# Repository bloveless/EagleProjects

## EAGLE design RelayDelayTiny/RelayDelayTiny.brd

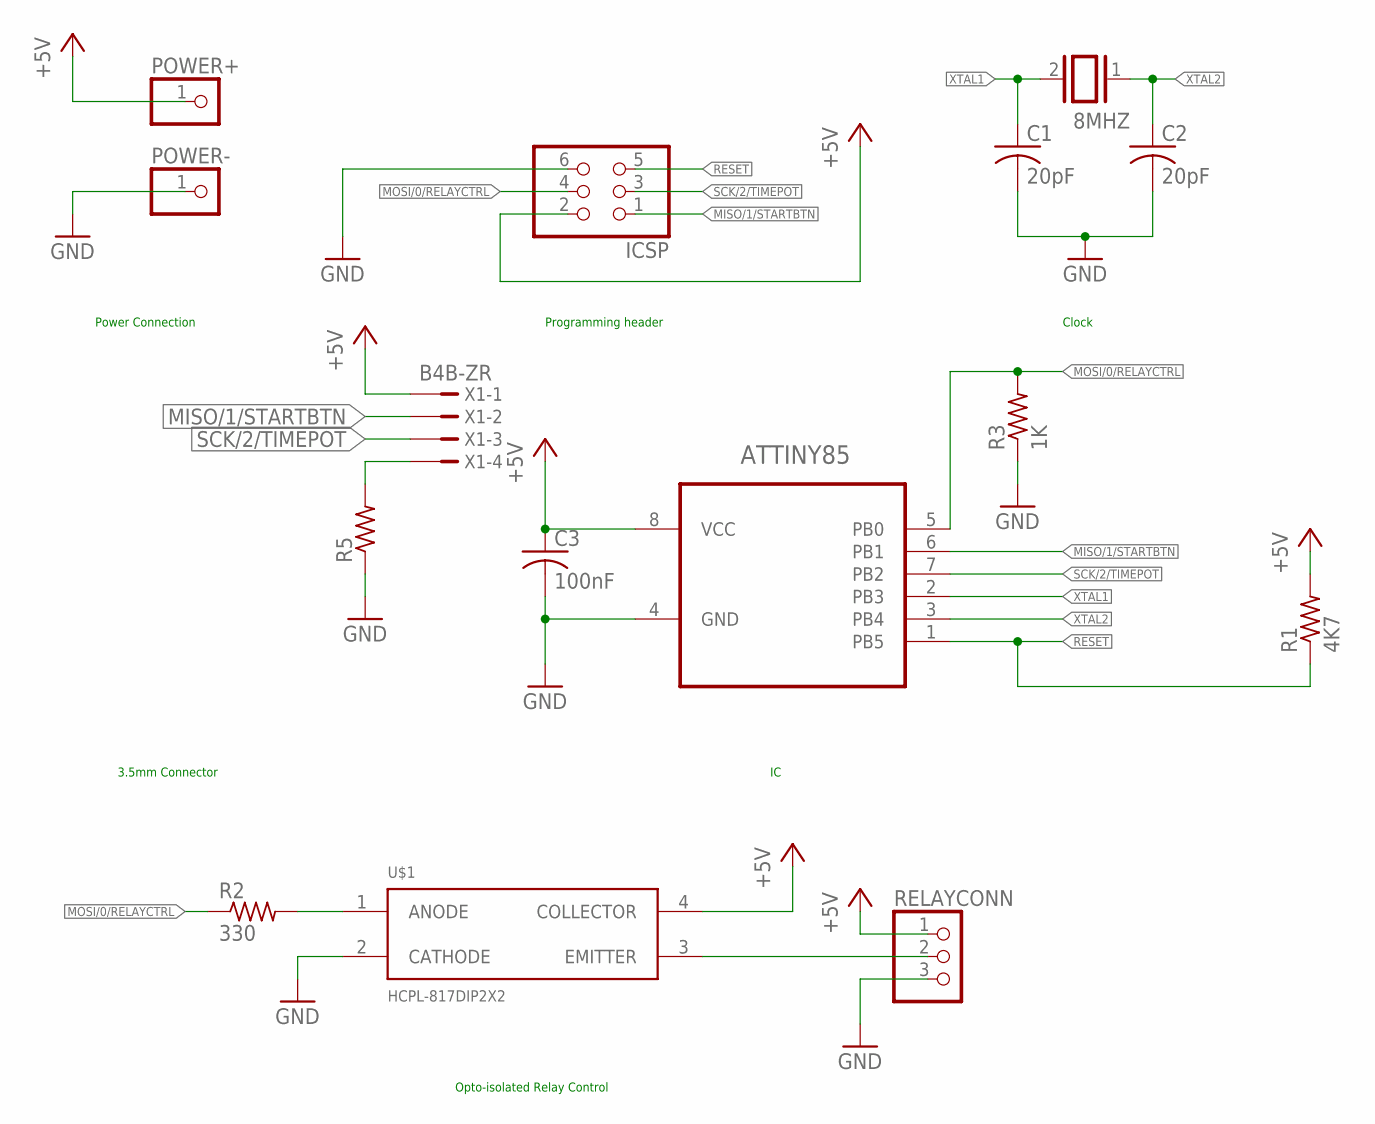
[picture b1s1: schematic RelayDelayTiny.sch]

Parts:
8MHZ: XTAL/S; QS
ATTINY85: ATTINY85-20SU; SOIC127P798X216-8N
C1, C2: 20pF; C0805
C3: 100nF; C0805
ICSP: PINHD-2X3; 2X03
POWER+: PINHD-1X1; 1X01
POWER-: PINHD-1X1; 1X01
R1: 4K7; R0805
R2: 330; M0805
R3: 1K; M0805
R5: R-US_R0805; R0805
RELAYCONN: PINHD-1X3; 1X03
U$1: HCPL-817DIP2X2; DIP
X1: B4B-ZR

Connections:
+5V: ATTINY85.8 (VCC), C3.1, ICSP.2, POWER+.1, R1.2, RELAYCONN.1, U$1.4 (COLLECTOR), X1.1
GND: ATTINY85.4 (GND), C1.2, C2.2, C3.2, ICSP.6, POWER-.1, R3.1, R5.1, RELAYCONN.3, U$1.2 (CATHODE)
MISO/1/STARTBTN: ATTINY85.6 (PB1), ICSP.1, X1.2
MOSI/0/RELAYCTRL: ATTINY85.5 (PB0), ICSP.4, R2.1, R3.2
unnamed: RELAYCONN.2, U$1.3 (EMITTER)
unnamed: R2.2, U$1.1 (ANODE)
unnamed: R5.2, X1.4
RESET: ATTINY85.1 (PB5), ICSP.5, R1.1
SCK/2/TIMEPOT: ATTINY85.7 (PB2), ICSP.3, X1.3
XTAL1: 8MHZ.2, ATTINY85.2 (PB3), C1.1
XTAL2: 8MHZ.1, ATTINY85.3 (PB4), C2.1

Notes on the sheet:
Programming header
Clock
3.5mm Connector
Opto-isolated Relay Control
Power Connection

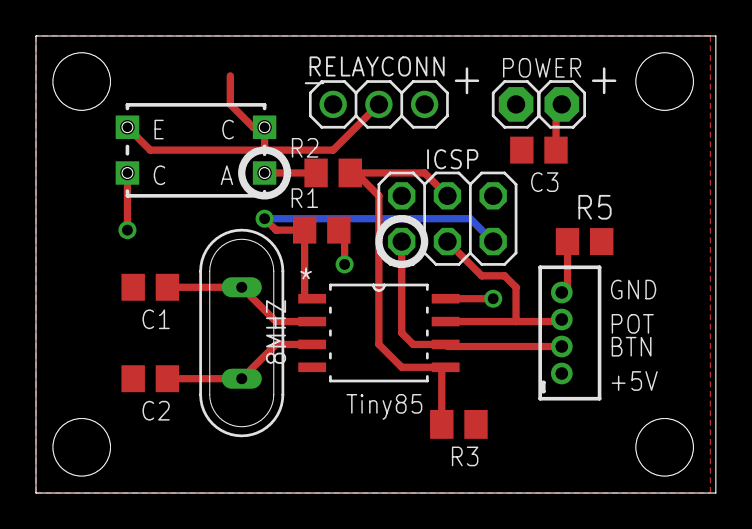
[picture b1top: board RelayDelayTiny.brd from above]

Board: 2 copper layers, 37.8 x 25.4 mm, 15 parts (0 on the bottom side), 11 nets.

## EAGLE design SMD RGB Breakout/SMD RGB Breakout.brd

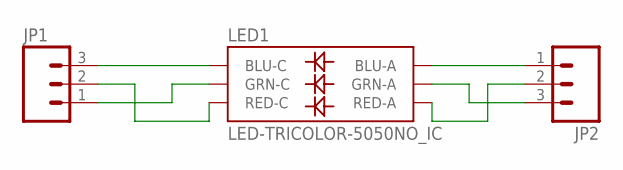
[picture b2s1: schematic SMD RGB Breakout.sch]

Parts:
JP1, JP2: M03PTH; 1X03
LED1: LED-TRICOLOR-5050NO_IC; LED-TRICOLOR-5050

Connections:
unnamed: JP1.3, LED1.4 (BLU-C)
unnamed: JP1.1, LED1.6 (GRN-C)
unnamed: JP1.2, LED1.5 (RED-C)
unnamed: JP2.1, LED1.3 (BLU-A)
unnamed: JP2.3, LED1.1 (GRN-A)
unnamed: JP2.2, LED1.2 (RED-A)

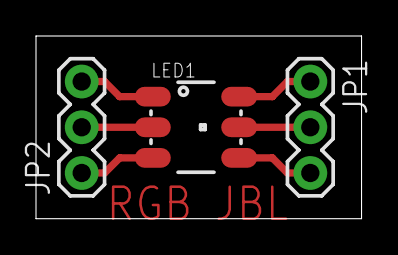
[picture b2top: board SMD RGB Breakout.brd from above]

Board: 2 copper layers, 18.1 x 10.2 mm, 3 parts (0 on the bottom side), 6 nets.

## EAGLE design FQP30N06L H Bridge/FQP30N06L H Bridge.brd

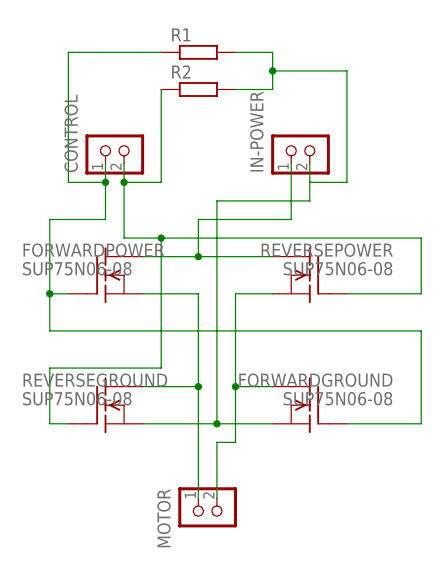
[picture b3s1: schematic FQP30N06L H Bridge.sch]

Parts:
CONTROL: CON_HEADER_1X02-PTH; M1X2
FORWARDGROUND: SUP75N06-08; TO220
FORWARDPOWER: SUP75N06-08; TO220
IN-POWER: CON_HEADER_1X02-PTH; M1X2
MOTOR: CON_HEADER_1X02-PTH; M1X2
R1, R2: RESISTOR-PTH-0.4; RTH025W
REVERSEGROUND: SUP75N06-08; TO220
REVERSEPOWER: SUP75N06-08; TO220

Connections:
unnamed: CONTROL.2, R2.1, REVERSEGROUND.1 (G), REVERSEPOWER.1 (G)
unnamed: CONTROL.1, FORWARDGROUND.1 (G), FORWARDPOWER.1 (G), R1.1
unnamed: FORWARDGROUND.3 (S), IN-POWER.2, R1.2, R2.2, REVERSEGROUND.3 (S)
unnamed: FORWARDPOWER.2 (D), IN-POWER.1, REVERSEPOWER.2 (D)
unnamed: FORWARDPOWER.3 (S), MOTOR.1, REVERSEGROUND.2 (D)
unnamed: FORWARDGROUND.2 (D), MOTOR.2, REVERSEPOWER.3 (S)

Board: 2 copper layers, 9 parts (0 on the bottom side), 6 nets, no tracks yet.

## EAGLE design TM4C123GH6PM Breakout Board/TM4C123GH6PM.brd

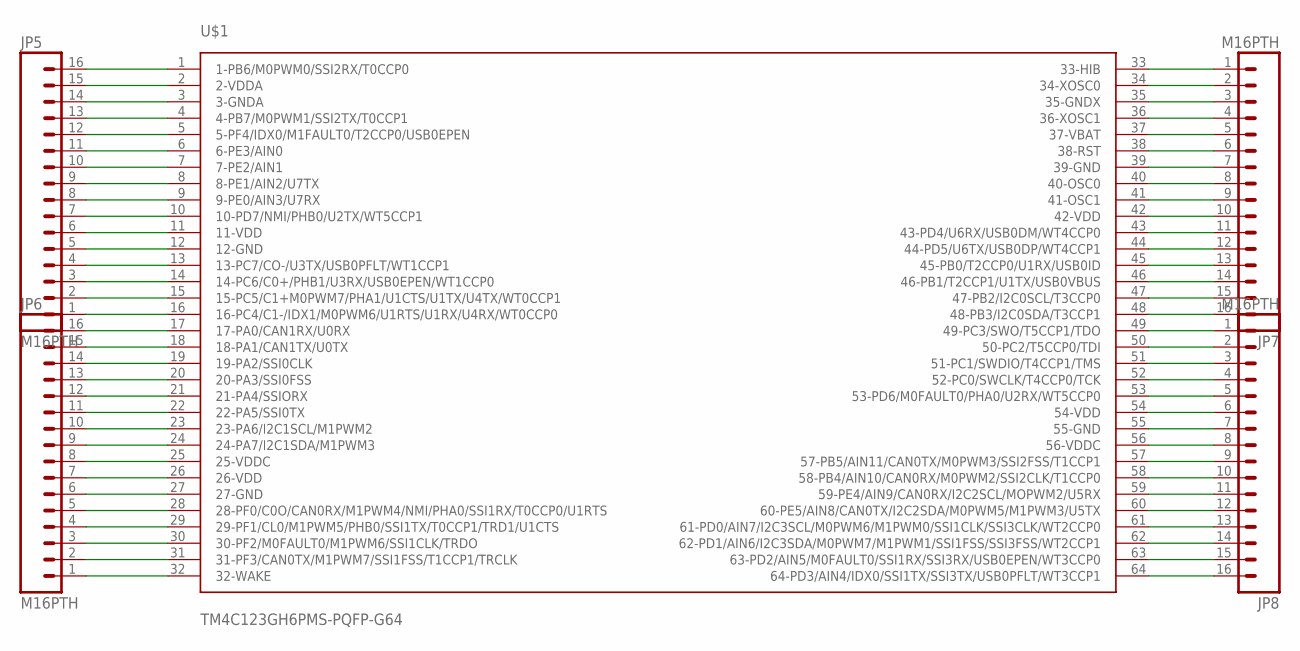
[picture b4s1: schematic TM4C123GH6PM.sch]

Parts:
JP5, JP6, JP7, JP8: M16PTH; 1X16
U$1: TM4C123GH6PMS-PQFP-G64; LQFP

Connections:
unnamed: JP5.16, U$1.1 (1-PB6/M0PWM0/SSI2RX/T0CCP0)
unnamed: JP5.15, U$1.2 (2-VDDA)
unnamed: JP5.14, U$1.3 (3-GNDA)
unnamed: JP5.13, U$1.4 (4-PB7/M0PWM1/SSI2TX/T0CCP1)
unnamed: JP5.12, U$1.5 (5-PF4/IDX0/M1FAULT0/T2CCP0/USB0EPEN)
unnamed: JP5.11, U$1.6 (6-PE3/AIN0)
unnamed: JP5.10, U$1.7 (7-PE2/AIN1)
unnamed: JP5.9, U$1.8 (8-PE1/AIN2/U7TX)
unnamed: JP5.8, U$1.9 (9-PE0/AIN3/U7RX)
unnamed: JP5.7, U$1.10 (10-PD7/NMI/PHB0/U2TX/WT5CCP1)
unnamed: JP5.6, U$1.11 (11-VDD)
unnamed: JP5.5, U$1.12 (12-GND)
unnamed: JP5.4, U$1.13 (13-PC7/CO-/U3TX/USB0PFLT/WT1CCP1)
unnamed: JP5.3, U$1.14 (14-PC6/C0+/PHB1/U3RX/USB0EPEN/WT1CCP0)
unnamed: JP5.2, U$1.15 (15-PC5/C1+M0PWM7/PHA1/U1CTS/U1TX/U4TX/W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)
unnamed: JP5.1, U$1.16 (16-PC4/C1-/IDX1/M0PWM6/U1RTS/U1RX/U4RX/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)
unnamed: JP6.16, U$1.17 (17-PA0/CAN1RX/U0RX)
unnamed: JP6.15, U$1.18 (18-PA1/CAN1TX/U0TX)
unnamed: JP6.14, U$1.19 (19-PA2/SSI0CLK)
unnamed: JP6.13, U$1.20 (20-PA3/SSI0FSS)
unnamed: JP6.12, U$1.21 (21-PA4/SSIORX)
unnamed: JP6.11, U$1.22 (22-PA5/SSI0TX)
unnamed: JP6.10, U$1.23 (23-PA6/I2C1SCL/M1PWM2)
unnamed: JP6.9, U$1.24 (24-PA7/I2C1SDA/M1PWM3)
unnamed: JP6.8, U$1.25 (25-VDDC)
unnamed: JP6.7, U$1.26 (26-VDD)
unnamed: JP6.6, U$1.27 (27-GND)
unnamed: JP6.5, U$1.28 (28-PF0/C0O/CAN0RX/M1PWM4/NMI/PHA0/SSI1R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)
unnamed: JP6.4, U$1.29 (29-PF1/CL0/M1PWM5/PHB0/SSI1TX/T0CCP1/TR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)
unnamed: JP6.3, U$1.30 (30-PF2/M0FAULT0/M1PWM6/SSI1CLK/TRDO)
unnamed: JP6.2, U$1.31 (31-PF3/CAN0TX/M1PWM7/SSI1FSS/T1CCP1/TRC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)
unnamed: JP6.1, U$1.32 (32-WAKE)
unnamed: JP7.1, U$1.33 (33-HIB)
unnamed: JP7.2, U$1.34 (34-XOSC0)
unnamed: JP7.3, U$1.35 (35-GNDX)
unnamed: JP7.4, U$1.36 (36-XOSC1)
unnamed: JP7.5, U$1.37 (37-VBAT)
unnamed: JP7.6, U$1.38 (38-RST)
unnamed: JP7.7, U$1.39 (39-GND)
unnamed: JP7.8, U$1.40 (40-OSC0)
unnamed: JP7.9, U$1.41 (41-OSC1)
unnamed: JP7.10, U$1.42 (42-VDD)
unnamed: JP7.11, U$1.43 (43-PD4/U6RX/USB0DM/WT4CCP0)
unnamed: JP7.12, U$1.44 (44-PD5/U6TX/USB0DP/WT4CCP1)
unnamed: JP7.13, U$1.45 (45-PB0/T2CCP0/U1RX/USB0ID)
unnamed: JP7.14, U$1.46 (46-PB1/T2CCP1/U1TX/USB0VBUS)
unnamed: JP7.15, U$1.47 (47-PB2/I2C0SCL/T3CCP0)
unnamed: JP7.16, U$1.48 (48-PB3/I2C0SDA/T3CCP1)
unnamed: JP8.1, U$1.49 (49-PC3/SWO/T5CCP1/TDO)
unnamed: JP8.2, U$1.50 (50-PC2/T5CCP0/TDI)
unnamed: JP8.3, U$1.51 (51-PC1/SWDIO/T4CCP1/TMS)
unnamed: JP8.4, U$1.52 (52-PC0/SWCLK/T4CCP0/TCK)
unnamed: JP8.5, U$1.53 (53-PD6/M0FAULT0/PHA0/U2RX/WT5CCP0)
unnamed: JP8.6, U$1.54 (54-VDD)
unnamed: JP8.7, U$1.55 (55-GND)
unnamed: JP8.8, U$1.56 (56-VDDC)
unnamed: JP8.9, U$1.57 (57-PB5/AIN11/CAN0TX/M0PWM3/SSI2FSS/T1CC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)
unnamed: JP8.10, U$1.58 (58-PB4/AIN10/CAN0RX/M0PWM2/SSI2CLK/T1CC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)
unnamed: JP8.11, U$1.59 (59-PE4/AIN9/CAN0RX/I2C2SCL/MOPWM2/U5RX)
unnamed: JP8.12, U$1.60 (60-PE5/AIN8/CAN0TX/I2C2SDA/M0PWM5/M1PWM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)
unnamed: JP8.13, U$1.61 (61-PD0/AIN7/I2C3SCL/M0PWM6/M1PWM0/SSI1C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)
unnamed: JP8.14, U$1.62 (62-PD1/AIN6/I2C3SDA/M0PWM7/M1PWM1/SSI1F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)
unnamed: JP8.15, U$1.63 (63-PD2/AIN5/M0FAULT0/SSI1RX/SSI3RX/USB0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)
unnamed: JP8.16, U$1.64 (64-PD3/AIN4/IDX0/SSI1TX/SSI3TX/USB0PFLT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)

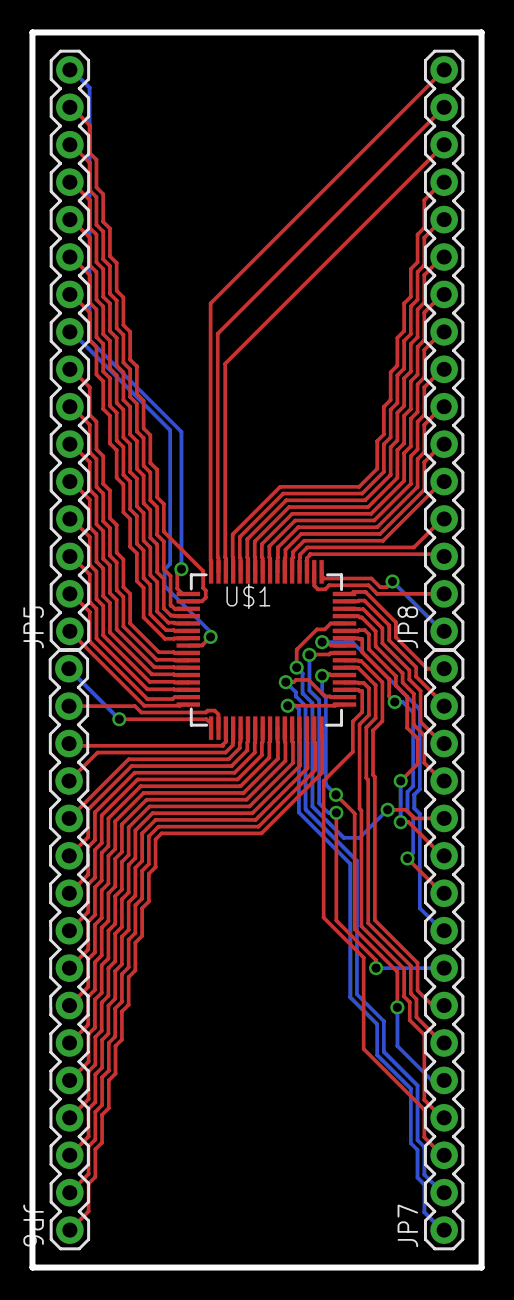
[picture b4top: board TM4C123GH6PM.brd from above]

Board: 2 copper layers, 30.5 x 83.8 mm, 5 parts (0 on the bottom side), 64 nets.

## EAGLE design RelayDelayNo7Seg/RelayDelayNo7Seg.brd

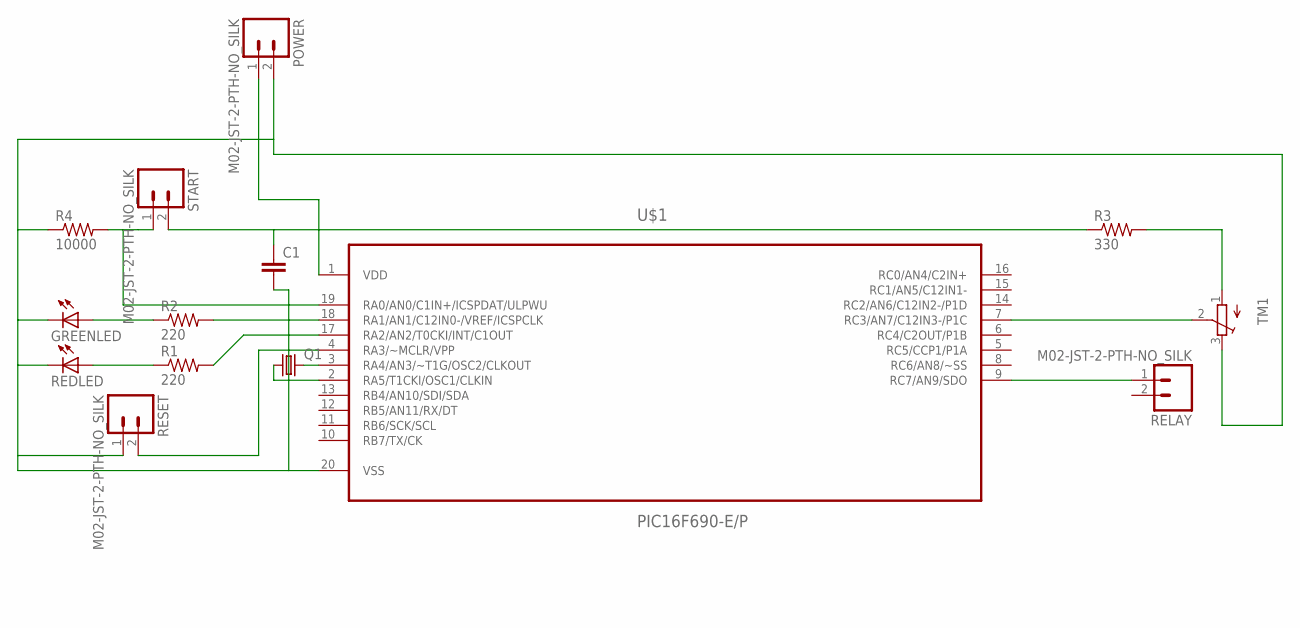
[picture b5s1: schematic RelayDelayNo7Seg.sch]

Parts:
C1: CAPEZ; CAP-PTH-SMALLEZ
GREENLED: LED5MM
POWER: M02-JST-2-PTH-NO_SILK; JST-2-PTH-NS
Q1: CRYSTALHC49S; HC49/S
R1, R2: 220; 0204V
R3: 330; 0204V
R4: 10000; 0204V
REDLED: LED5MM
RELAY: M02-JST-2-PTH-NO_SILK; JST-2-PTH-NS
RESET: M02-JST-2-PTH-NO_SILK; JST-2-PTH-NS
START: M02-JST-2-PTH-NO_SILK; JST-2-PTH-NS
TM1: TRIMPOT3386; TRIM-3386
U$1: PIC16F690-E/P; DIP254P762X533-20

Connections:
unnamed: R2.2, U$1.18 (RA1/AN1/C12IN0-/VREF/ICSPCLK)
unnamed: GREENLED.A, R2.1
unnamed: R1.2, U$1.17 (RA2/AN2/T0CKI/INT/C1OUT)
unnamed: R1.1, REDLED.A
unnamed: TM1.2 (S), U$1.7 (RC3/AN7/C12IN3-/P1C)
unnamed: R3.2, TM1.1 (A)
unnamed: RESET.2, U$1.4 (RA3/~MCLR/VPP)
unnamed: Q1.1, U$1.2 (RA5/T1CKI/OSC1/CLKIN)
unnamed: R4.2, START.1, U$1.19 (RA0/AN0/C1IN+/ICSPDAT/ULPWU)
unnamed: RELAY.1, U$1.9 (RC7/AN9/SDO)
unnamed: Q1.2, U$1.3 (RA4/AN3/~T1G/OSC2/CLKOUT)
unnamed: C1.1, POWER.1, R3.1, START.2, U$1.1 (VDD)
unnamed: C1.2, GREENLED.K (C), POWER.2, R4.1, REDLED.K (C), RESET.1, TM1.3 (E), U$1.20 (VSS)

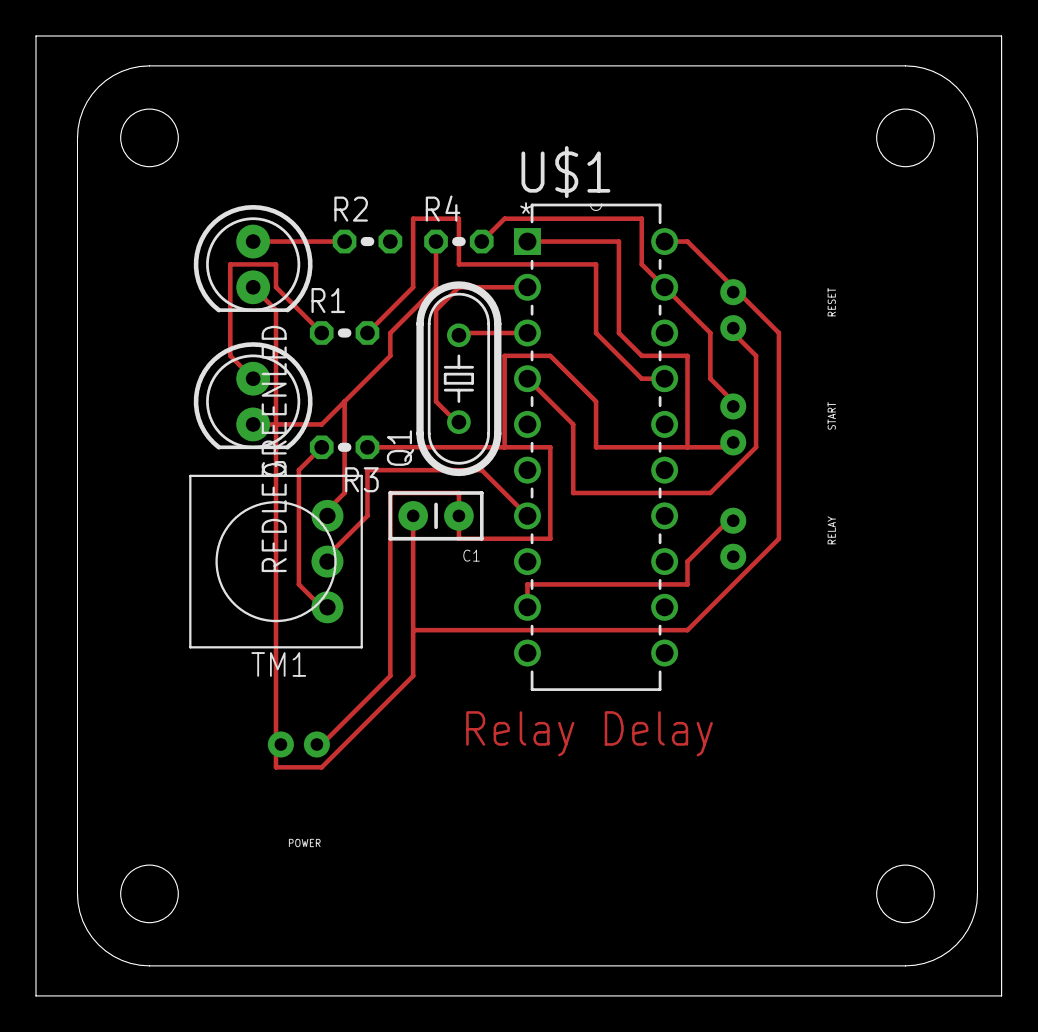
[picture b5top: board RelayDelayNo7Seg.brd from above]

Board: 2 copper layers, 53.6 x 53.3 mm, 15 parts (0 on the bottom side), 13 nets.

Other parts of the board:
U$2: DP5050_V1

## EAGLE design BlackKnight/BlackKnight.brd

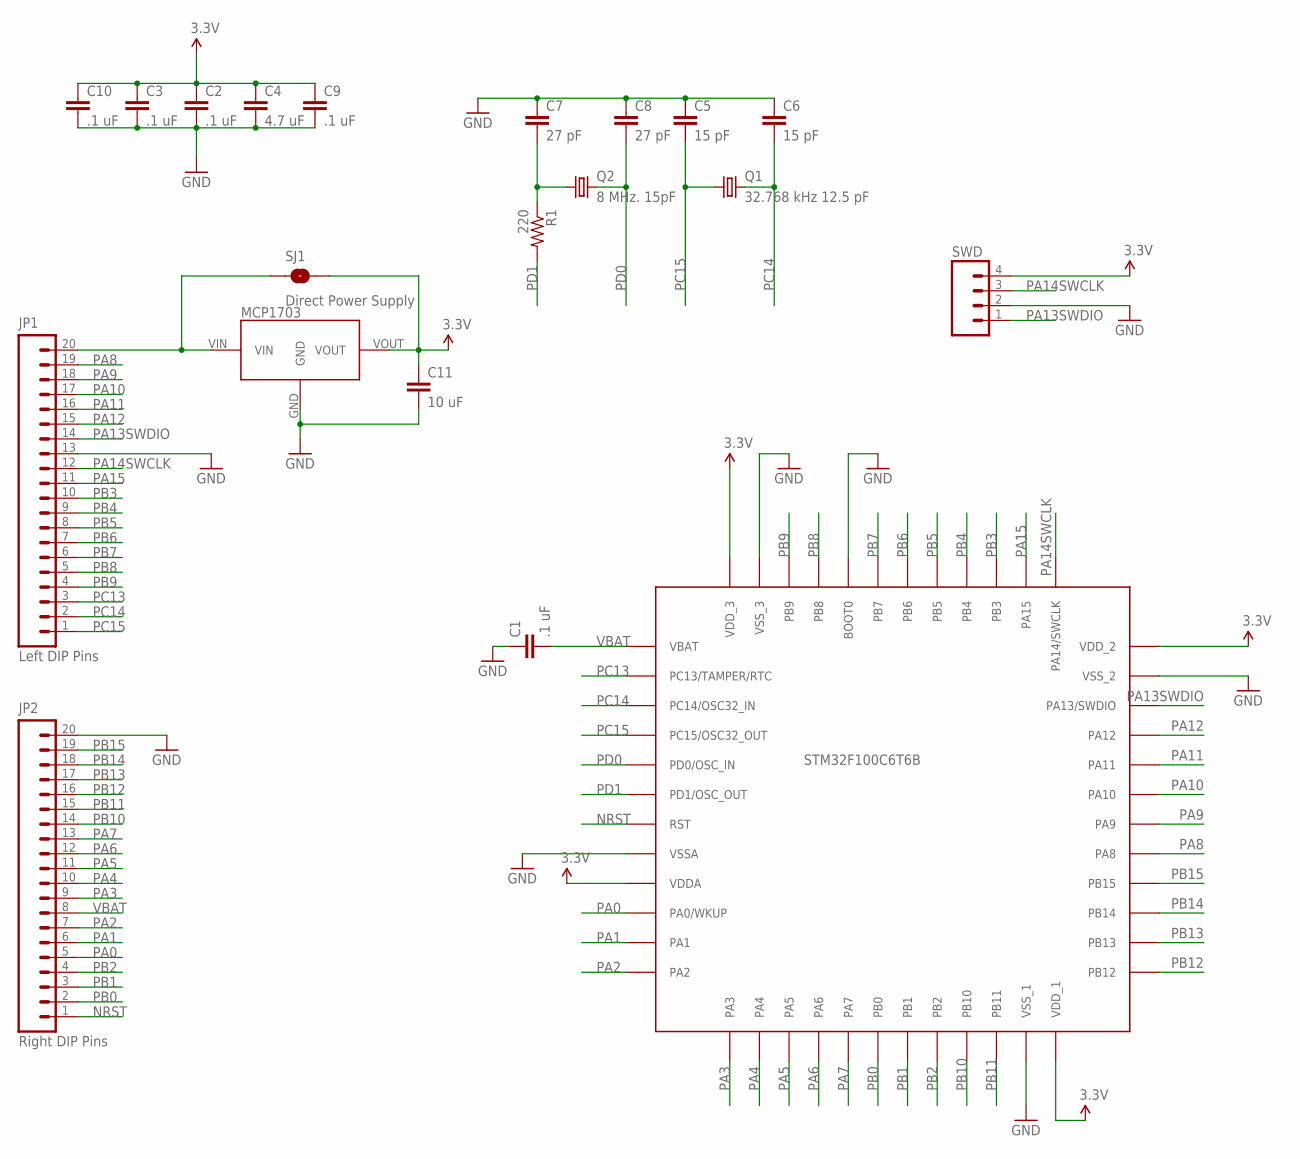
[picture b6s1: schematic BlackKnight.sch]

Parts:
C1, C2, C3, C9, C10: .1 uF; 0805
C4: 4.7 uF; 0805
C5, C6: 15 pF; 0805
C7, C8: 27 pF; 0805
C11: 10 uF; 0805
JP1: Left DIP Pins; 1X20
JP2: Right DIP Pins; 1X20
MCP1703: MCP1703; SOT-89
Q1: 32.768 kHz 12.5 pF; TC26H
Q2: 8 MHz. 15pF; HC49U-V
R1: 220; 0805
SJ1: Direct Power Supply; SJ_2S-NO
STM32F100C6T6B: STM32F100C6T6B; 48-LQFP
SWD: M04LOCK; 1X04_LOCK

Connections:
3.3V: C2.1, C3.1, C4.1, C9.1, C10.1, C11.1, MCP1703.VOUT, SJ1.2, STM32F100C6T6B.VDDA, STM32F100C6T6B.VDD_1, STM32F100C6T6B.VDD_2, STM32F100C6T6B.VDD_3, SWD.4
GND: C1.1, C2.2, C3.2, C4.2, C5.1, C6.1, C7.1, C8.1, C9.2, C10.2, C11.2, JP1.13, JP2.20, MCP1703.GND, STM32F100C6T6B.BOOT0, STM32F100C6T6B.VSSA, STM32F100C6T6B.VSS_1, STM32F100C6T6B.VSS_2, STM32F100C6T6B.VSS_3, SWD.2
unnamed: JP1.20, MCP1703.VIN, SJ1.1
unnamed: C7.2, Q2.1, R1.1
NRST: JP2.1, STM32F100C6T6B.RST
PA0: JP2.5, STM32F100C6T6B.PA0/WKUP
PA1: JP2.6, STM32F100C6T6B.PA1
PA2: JP2.7, STM32F100C6T6B.PA2
PA3: JP2.9, STM32F100C6T6B.PA3
PA4: JP2.10, STM32F100C6T6B.PA4
PA5: JP2.11, STM32F100C6T6B.PA5
PA6: JP2.12, STM32F100C6T6B.PA6
PA7: JP2.13, STM32F100C6T6B.PA7
PA8: JP1.19, STM32F100C6T6B.PA8
PA9: JP1.18, STM32F100C6T6B.PA9
PA10: JP1.17, STM32F100C6T6B.PA10
PA11: JP1.16, STM32F100C6T6B.PA11
PA12: JP1.15, STM32F100C6T6B.PA12
PA13SWDIO: JP1.14, STM32F100C6T6B.PA13/SWDIO, SWD.1
PA14SWCLK: JP1.12, STM32F100C6T6B.PA14/SWCLK, SWD.3
PA15: JP1.11, STM32F100C6T6B.PA15
PB0: JP2.2, STM32F100C6T6B.PB0
PB1: JP2.3, STM32F100C6T6B.PB1
PB2: JP2.4, STM32F100C6T6B.PB2
PB3: JP1.10, STM32F100C6T6B.PB3
PB4: JP1.9, STM32F100C6T6B.PB4
PB5: JP1.8, STM32F100C6T6B.PB5
PB6: JP1.7, STM32F100C6T6B.PB6
PB7: JP1.6, STM32F100C6T6B.PB7
PB8: JP1.5, STM32F100C6T6B.PB8
PB9: JP1.4, STM32F100C6T6B.PB9
PB10: JP2.14, STM32F100C6T6B.PB10
PB11: JP2.15, STM32F100C6T6B.PB11
PB12: JP2.16, STM32F100C6T6B.PB12
PB13: JP2.17, STM32F100C6T6B.PB13
PB14: JP2.18, STM32F100C6T6B.PB14
PB15: JP2.19, STM32F100C6T6B.PB15
PC13: JP1.3, STM32F100C6T6B.PC13/TAMPER/RTC
PC14: C6.2, JP1.2, Q1.2, STM32F100C6T6B.PC14/OSC32_IN
PC15: C5.2, JP1.1, Q1.1, STM32F100C6T6B.PC15/OSC32_OUT
PD0: C8.2, Q2.2, STM32F100C6T6B.PD0/OSC_IN
PD1: R1.2, STM32F100C6T6B.PD1/OSC_OUT
VBAT: C1.2, JP2.8, STM32F100C6T6B.VBAT

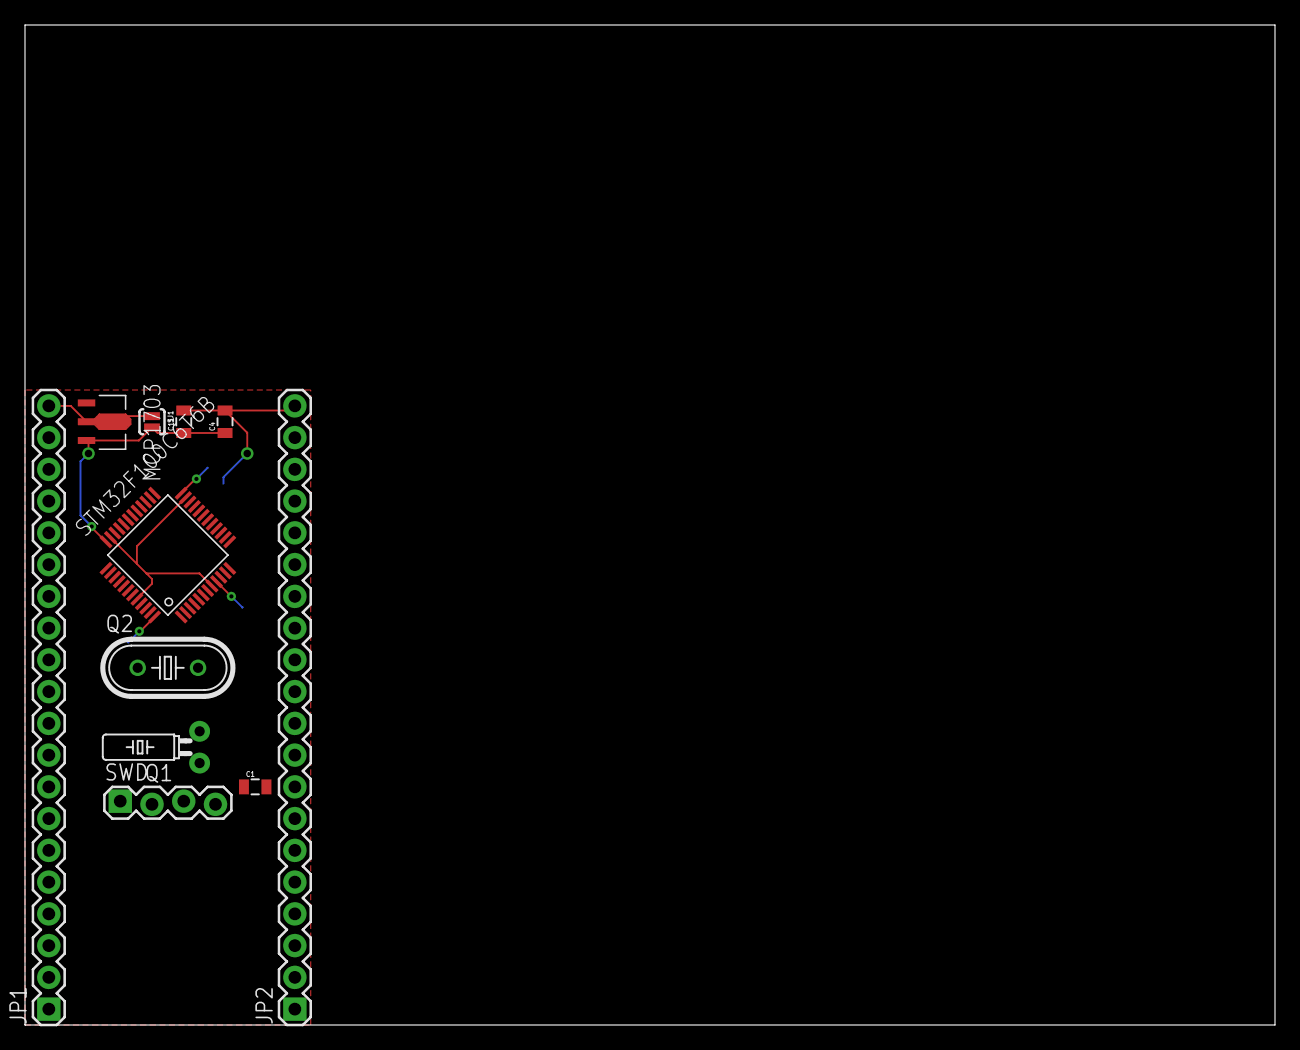
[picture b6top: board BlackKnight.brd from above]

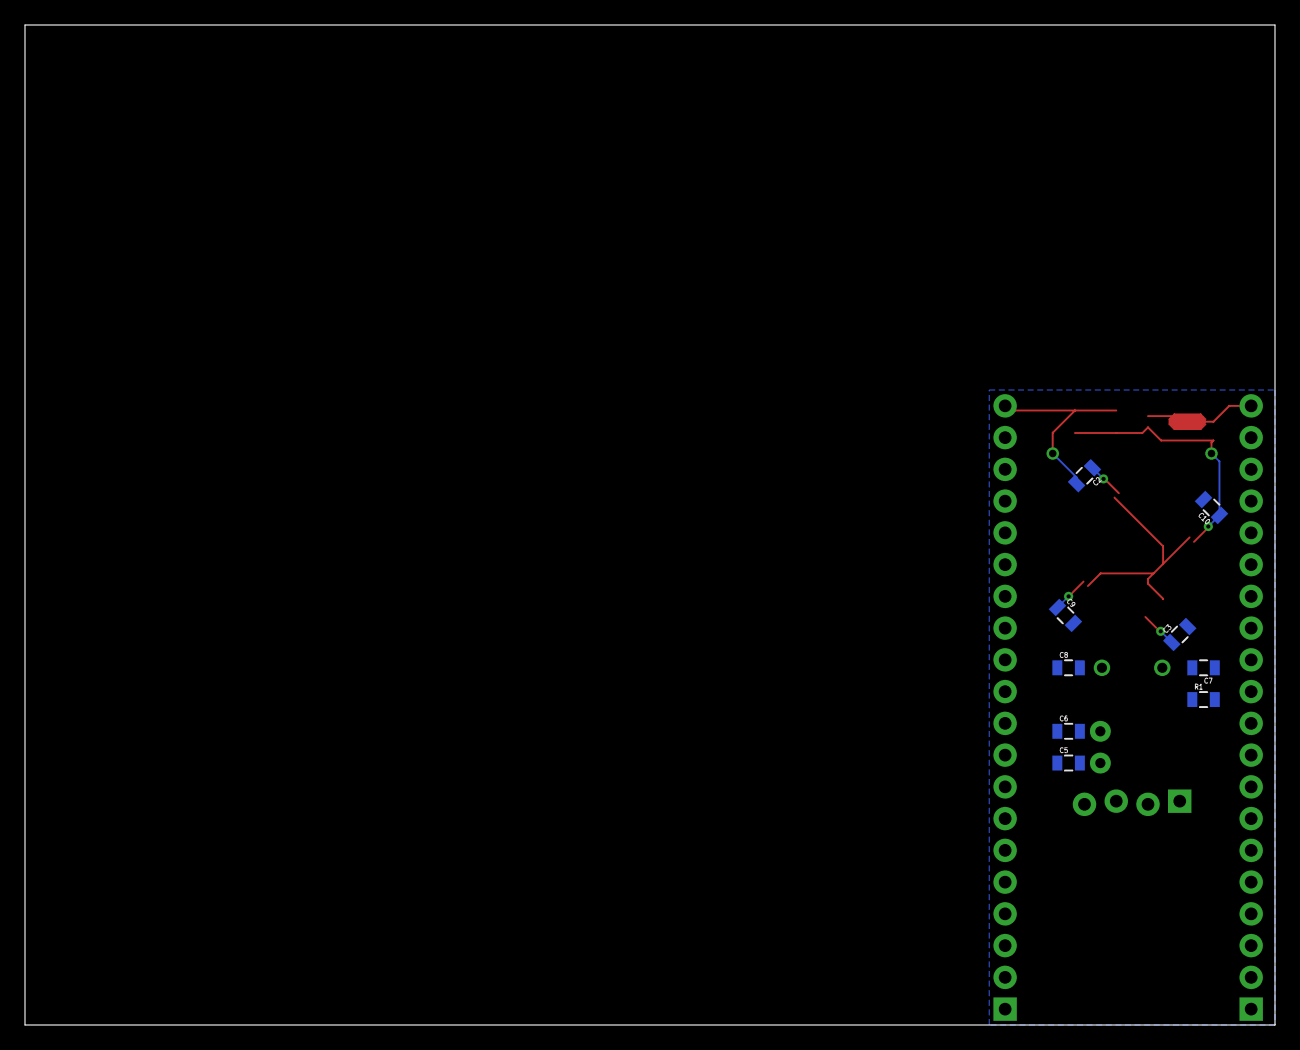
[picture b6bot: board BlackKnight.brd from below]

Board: 2 copper layers, 100.0 x 80.0 mm, 20 parts (9 on the bottom side), 43 nets.

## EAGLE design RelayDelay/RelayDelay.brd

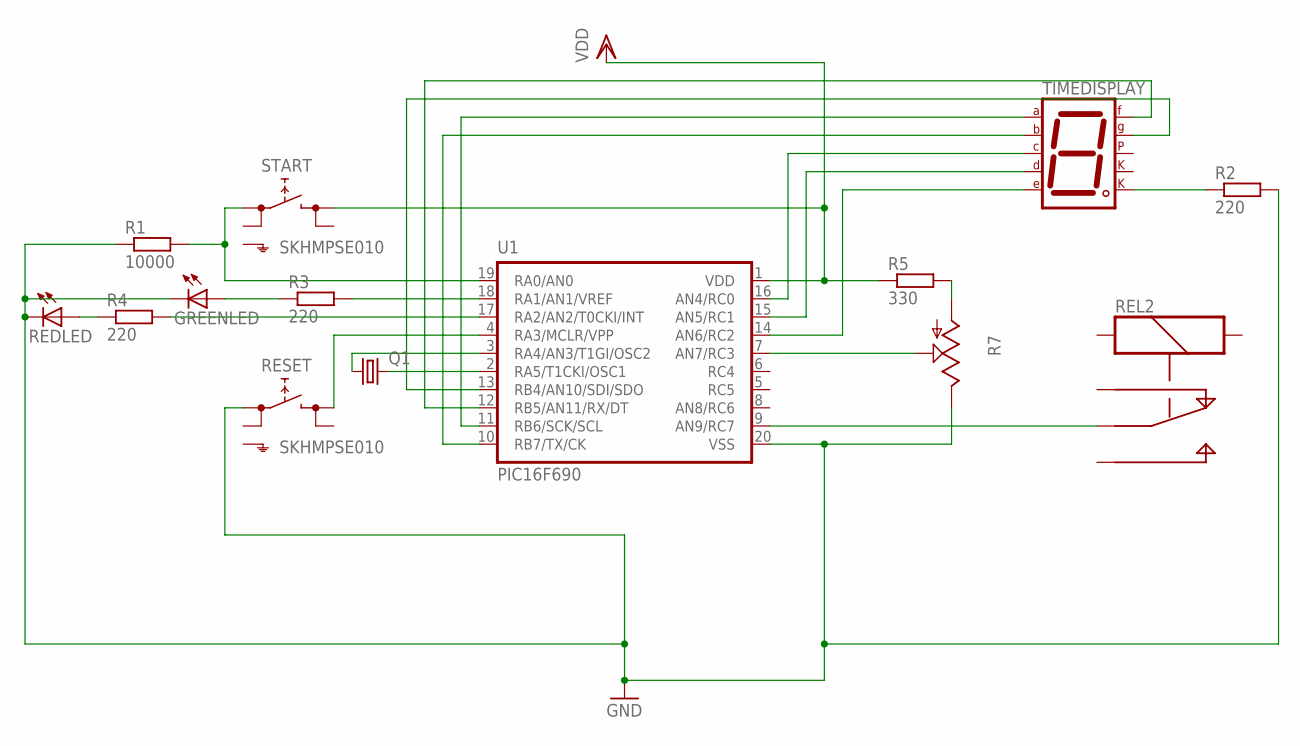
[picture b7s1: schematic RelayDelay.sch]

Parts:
GREENLED: LED; SMARTLED-TTW
Q1: CRYSTALHC49S; HC49/S
R1: 10000; 0204/5
R2, R3, R4: 220; 0204/5
R5: 330; 0204/5
R7: TRIM_US-CIP20C-6MM; CIP20C-6MM
REDLED: LED; SMARTLED-TTW
REL2: REL-5PIN
RESET: SKHMPSE010; SKHMPXE010
START: SKHMPSE010; SKHMPXE010
TIMEDISPLAY: 7SEG-CK; 7SEG-13
U1: PIC16F690; DIL20

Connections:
GND: GREENLED.C@1 (C), R1.1, R2.2, R7.E, REDLED.C@1 (C), RESET.1 (1.1), U1.20 (VSS)
unnamed: R4.2, U1.17 (RA2/AN2/T0CKI/INT)
unnamed: R1.2, START.1 (1.1), U1.19 (RA0/AN0)
unnamed: Q1.2, U1.2 (RA5/T1CKI/OSC1)
unnamed: Q1.1, U1.3 (RA4/AN3/T1GI/OSC2)
unnamed: GREENLED.A@1 (A), R3.1
unnamed: R4.1, REDLED.A@1 (A)
unnamed: RESET.3 (2.1), U1.4 (RA3/MCLR/VPP)
unnamed: R3.2, U1.18 (RA1/AN1/VREF)
unnamed: R5.2, R7.A
unnamed: R2.1, TIMEDISPLAY.8 (CK2)
unnamed: R7.S, U1.7 (AN7/RC3)
unnamed: TIMEDISPLAY.7 (A), U1.11 (RB6/SCK/SCL)
unnamed: TIMEDISPLAY.6 (B), U1.10 (RB7/TX/CK)
unnamed: TIMEDISPLAY.4 (C), U1.16 (AN4/RC0)
unnamed: TIMEDISPLAY.2 (D), U1.15 (AN5/RC1)
unnamed: TIMEDISPLAY.1 (E), U1.14 (AN6/RC2)
unnamed: TIMEDISPLAY.9 (F), U1.12 (RB5/AN11/RX/DT)
unnamed: TIMEDISPLAY.10 (G), U1.13 (RB4/AN10/SDI/SDO)
unnamed: REL2.C, U1.9 (AN9/RC7)
VDD: R5.1, START.3 (2.1), U1.1 (VDD)

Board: 2 copper layers, 14 parts (1 on the bottom side), 21 nets, no tracks yet.

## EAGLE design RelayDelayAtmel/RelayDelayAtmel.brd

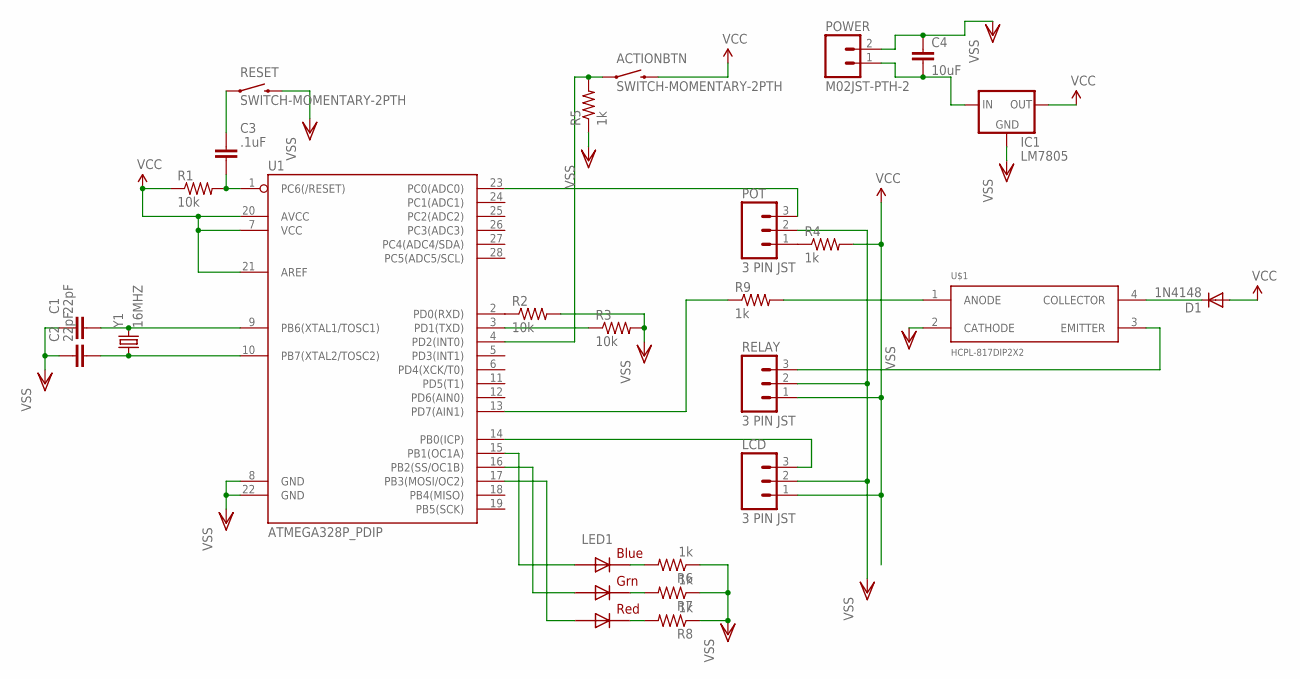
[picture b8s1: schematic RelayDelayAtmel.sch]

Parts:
ACTIONBTN: SWITCH-MOMENTARY-2PTH; TACTILE-PTH
C1, C2: 22pF; C0.1PTH
C3: .1uF; C0.1PTH
C4: 10uF; CAP-PTH-SMALLEZ
D1: 1N4148; DIODE-1N4001-KIT
IC1: LM7805; TO-220-ALT
LCD: 3 PIN JST; JST-3-PTH
LED1: RGBLED5050
POT: 3 PIN JST; JST-3-PTH
POWER: M02JST-PTH-2; JST-2-PTH
R1, R2, R3: 10k; AXIAL-0.3
R4, R5, R6, R7, R8, R9: 1k; AXIAL-0.3
RELAY: 3 PIN JST; JST-3-PTH
RESET: SWITCH-MOMENTARY-2PTH; TACTILE-PTH
U1: ATMEGA328P_PDIP; DIL28-3
U$1: HCPL-817DIP2X2; DIP
Y1: 16MHZ; HC49US

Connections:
unnamed: C1.2, U1.9 (PB6(XTAL1/TOSC1)), Y1.2
unnamed: C2.2, U1.10 (PB7(XTAL2/TOSC2)), Y1.1
unnamed: C3.2, R1.P$2 (2), U1.1 (PC6(/RESET))
unnamed: C3.1, RESET.1
unnamed: R3.P$1 (1), U1.3 (PD1(TXD))
unnamed: R2.P$1 (1), U1.2 (PD0(RXD))
unnamed: C4.2, IC1.IN, POWER.1
unnamed: D1.C, U$1.4 (COLLECTOR)
unnamed: RELAY.3, U$1.3 (EMITTER)
unnamed: POT.1, R4.P$1 (1)
unnamed: ACTIONBTN.1, R5.P$2 (2), U1.4 (PD2(INT0))
unnamed: LED1.4 (BLUE_C), R6.P$2 (2)
unnamed: LED1.6 (GREEN_C), R7.P$2 (2)
unnamed: LED1.5 (RED_C), R8.P$2 (2)
unnamed: LED1.3 (BLUE_A), U1.15 (PB1(OC1A))
unnamed: LED1.1 (GREEN_A), U1.16 (PB2(SS/OC1B))
unnamed: LED1.2 (RED_A), U1.17 (PB3(MOSI/OC2))
unnamed: POT.3, U1.23 (PC0(ADC0))
unnamed: LCD.3, U1.14 (PB0(ICP))
unnamed: R9.P$2 (2), U$1.1 (ANODE)
unnamed: R9.P$1 (1), U1.13 (PD7(AIN1))
VCC: ACTIONBTN.3 (2), D1.A, IC1.OUT, LCD.1, R1.P$1 (1), R4.P$2 (2), RELAY.1, U1.7 (VCC), U1.20 (AVCC), U1.21 (AREF)
VSS: C1.1, C2.1, C4.1, IC1.GND, LCD.2, POT.2, POWER.2, R2.P$2 (2), R3.P$2 (2), R5.P$1 (1), R6.P$1 (1), R7.P$1 (1), R8.P$1 (1), RELAY.2, RESET.3 (2), U1.8 (GND), U1.22 (GND), U$1.2 (CATHODE)

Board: 2 copper layers, 25 parts (0 on the bottom side), 23 nets, no tracks yet.

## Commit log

2015-04-11 Inital commit of all my eagle projects
2015-04-11 Remove DS_Store and add to gitignore

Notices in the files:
parts and their libraries:
SparkFun-Capacitors: Licensing: Creative Commons ShareAlike 4.0 International - https://creativecommons.org/licenses/by-sa/4.0
SparkFun-DigitalIC: Licensing: CC v3.0 Share-Alike You are welcome to use this library for commercial purposes.
